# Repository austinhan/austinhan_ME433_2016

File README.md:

Austin Han
3/31/2016
...
Another line

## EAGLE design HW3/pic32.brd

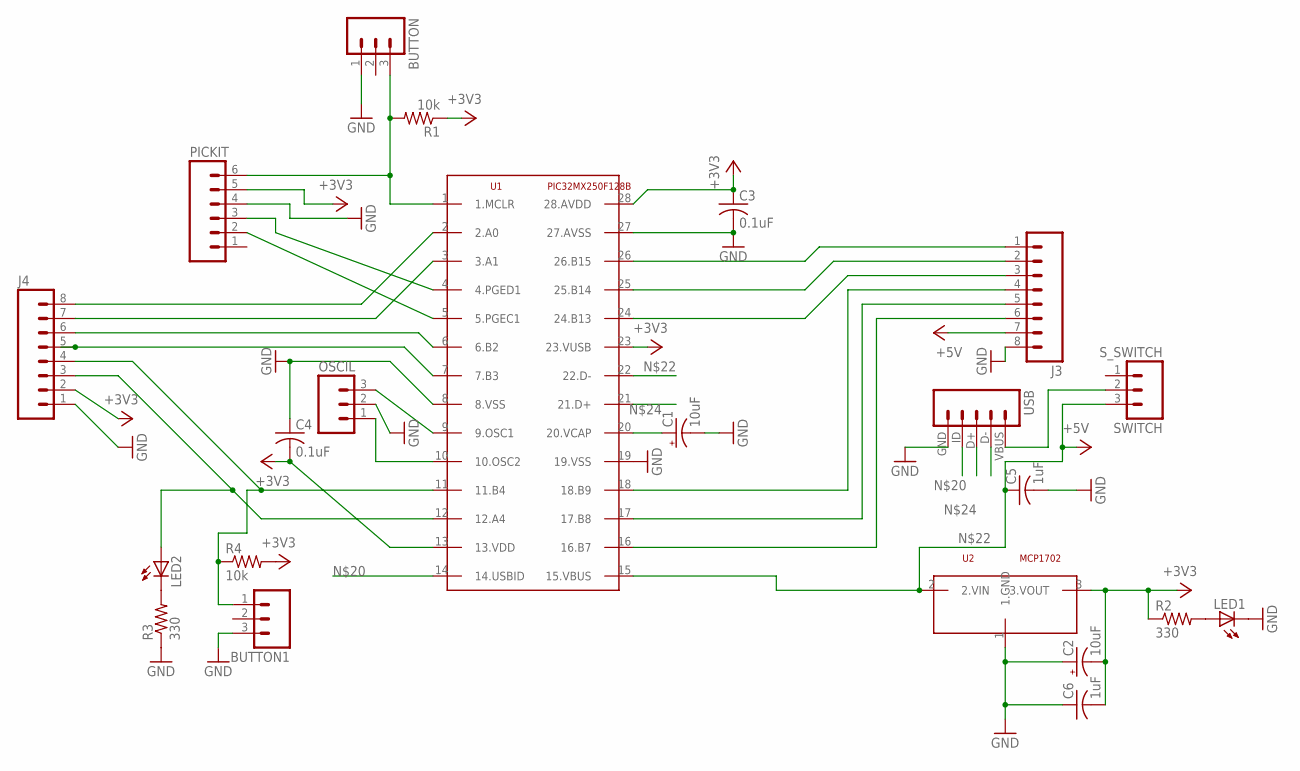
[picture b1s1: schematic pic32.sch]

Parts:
BUTTON, BUTTON1: M03PTH; 1X03
C1, C2: 10uF; TT2D4
C3, C4: 0.1uF; C025-024X044
C5, C6: 1uF; C025-024X044
J3, J4: M08; 1X08_ROUND
LED1, LED2: LED3MM
OSCIL: M03PTH; 1X03
PICKIT: M06SILK_FEMALE_PTH; 1X06
R1, R4: 10k; 0207/7
R2, R3: 330; 0207/7
SWITCH: S_SWITCH
U1: PIC32MX250F128B; DIL28-3
U2: MCP1702; TO92
USB: M05; USB-MB-H

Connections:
+3V3: C2.-, C3.1, C4.2, C6.2, J4.2, PICKIT.5, R1.1, R2.1, R4.2, U1.13 (13.VDD), U1.23 (23.VUSB), U1.28 (28.AVDD), U2.3 (3.VOUT)
+5V: C5.1, J3.7, SWITCH.3, U1.15 (15.VBUS), U2.2 (2.VIN)
GND: BUTTON.1, BUTTON1.3, C1.-, C2.+, C3.2, C4.1, C5.2, C6.1, J3.8, J4.1, LED1.K (C), OSCIL.2, PICKIT.4, R3.1, U1.8 (8.VSS), U1.19 (19.VSS), U1.27 (27.AVSS), U2.1 (1.GND), USB.GND (1)
unnamed: C1.+, U1.20 (20.VCAP)
unnamed: PICKIT.2, U1.5 (5.PGEC1)
unnamed: PICKIT.3, U1.4 (4.PGED1)
unnamed: BUTTON.3, PICKIT.6, R1.2, U1.1 (1.MCLR)
unnamed: J3.1, U1.26 (26.B15)
unnamed: J3.2, U1.25 (25.B14)
unnamed: J3.3, U1.24 (24.B13)
unnamed: J3.4, U1.18 (18.B9)
unnamed: J3.5, U1.17 (17.B8)
unnamed: J3.6, U1.16 (16.B7)
unnamed: J4.8, U1.2 (2.A0)
unnamed: J4.7, U1.3 (3.A1)
unnamed: J4.6, U1.6 (6.B2)
unnamed: BUTTON1.1, J4.4, R4.1, U1.11 (11.B4)
unnamed: J4.3, LED2.A, U1.12 (12.A4)
unnamed: OSCIL.3, U1.9 (9.OSC1)
unnamed: J4.5, U1.7 (7.B3)
unnamed: OSCIL.1, U1.10 (10.OSC2)
unnamed: U1.14 (14.USBID), USB.ID (2)
unnamed: SWITCH.2, USB.VBUS (5)
unnamed: U1.22 (22.D-), USB.D- (4)
unnamed: LED1.A, R2.2
unnamed: U1.21 (21.D+), USB.D+ (3)
unnamed: LED2.K (C), R3.2

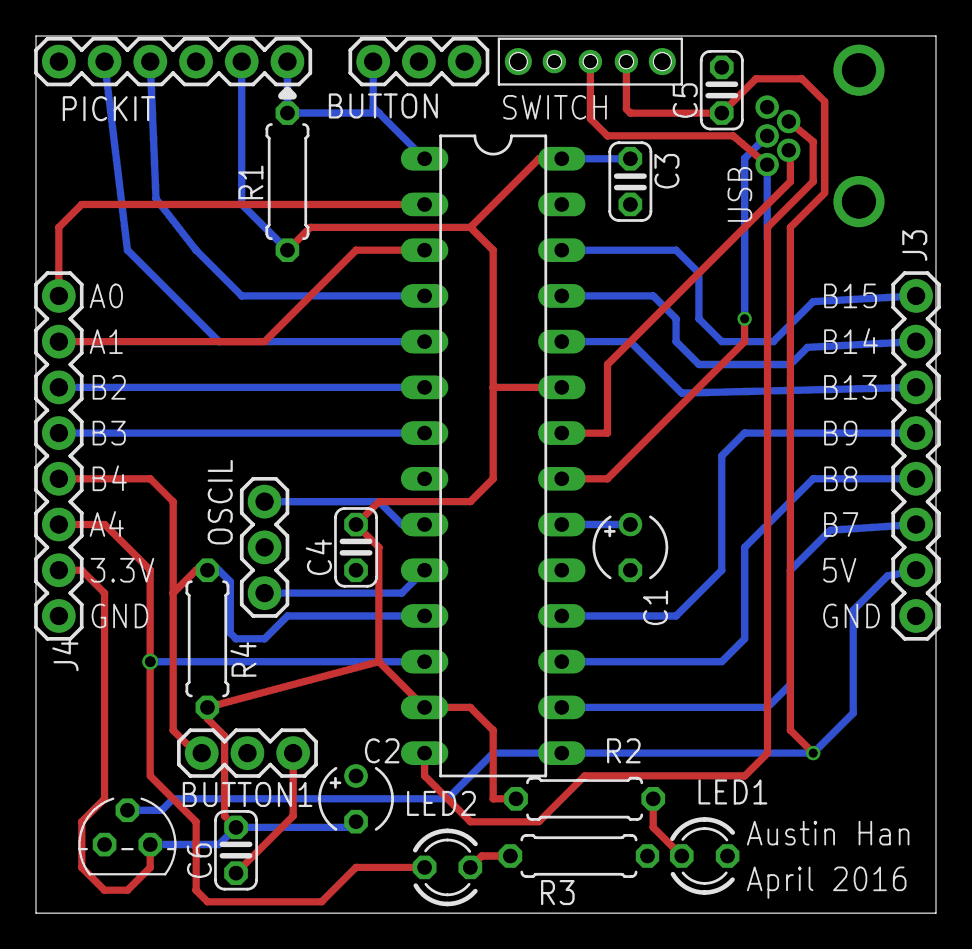
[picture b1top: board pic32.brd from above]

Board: 2 copper layers, 50.0 x 48.7 mm, 22 parts (0 on the bottom side), 27 nets.

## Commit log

2016-03-31 :circus_tent: Added .gitattributes & .gitignore files
2016-03-31 My first commit!
2016-03-31 Added line
2016-04-03 hw1 parts 1/2
2016-04-03 circuit diagram edit
2016-04-03 Breadboard picture
2016-04-03 created main.c
2016-04-03 completed code
2016-04-04 final corrected code, circuit diagram
2016-04-14 HW3
    Ready to be checked before order
2016-05-05 HW5 Part 1
    characters appear upside down for some reason
2016-05-05 Completed HW5
2016-05-30 CAD stuff
2016-06-05 HW11-13
2016-06-07 HW14-16
2016-06-09 Completed HW7/8 - All HW done
2016-06-09 USB Mouse video demo
